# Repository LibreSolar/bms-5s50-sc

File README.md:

# BMS 5s (12 V)

Battery management system for up to 5 Li-ion cells based on bq76920 IC from Texas Instruments

## Boards

The Libre Solar BMS is divided into two different boards, connected via a flat cable and integrated into one housing.

### Control board (BMS 5s)

[Schematic (PDF)](power-pcb/Switch-N-Sense.pdf)

### Power board (Switch-N-Sense)

[Schematic (PDF)](control-pcb/BMS-5s.pdf)

## Features

- 3 to 5 Li-ion cells (e.g. LiFePO4)
- 50 A maximum current
- Balancing current approx. 150 mA
- STM32F072 ARM Cortex M0 microcontroller
- Built-in CAN communication interface and UEXT extension connector

## Housing

The BMS should fit into a Hammond Mfg 1591XXBFL housing as shown in below picture. The picture shows the BMS controller PCB with the Switch-N-Sense power PCB stacked on top of it:

## History

- There is [another version of the BMS](https://github.com/LibreSolar/BMS48V)  supporting more cells and developed in Eagle CAD. This one is the first of the new BMS generation developed in KiCad. An updated version of the versions with higher number of cells might come soon.

## Important Notice

The PCBs have not been tested regarding EMC and other regulations. If you reproduce the boards, you use them at your own risk and responsibility.

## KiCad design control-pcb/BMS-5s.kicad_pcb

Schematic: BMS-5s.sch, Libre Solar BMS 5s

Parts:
LOGO1: OPEN_HARDWARE; OSHW-Logo_5.7x6mm_SilkScreen
LOGO2: LIBRE_SOLAR; LIBRESOLAR_LOGO
P1: Conn_Switch-N-Sense; Wuerth_WR-FPC_686112148922; PartNumber 686112148922
P2: CONN_01X06; Phoenix_Contact_MC_1,5_6-G-3,81; PartNumber 1803316
TP3: Load+; TestPoint_0.8mm_hole
TP4: Bat+; TestPoint_0.8mm_hole
TP5: Regout; TestPoint_0.8mm_hole
TP6: SDA; TestPoint_0.8mm_hole
TP7: SCL; TestPoint_0.8mm_hole

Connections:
/Analog Frontend/BAT+: P1.1, TP4.1; also elsewhere on the board
/Analog Frontend/LOAD+: P1.2, TP3.1; also elsewhere on the board
/BQ76920/CELLS_0: P2.6; also elsewhere on the board
/BQ76920/CELLS_1: P2.5; also elsewhere on the board
/BQ76920/CELLS_2: P2.4; also elsewhere on the board
/BQ76920/CELLS_3: P2.3; also elsewhere on the board
/BQ76920/CELLS_4: P2.2; also elsewhere on the board
/BQ76920/CELLS_5: P2.1; also elsewhere on the board
/BQ76920/CHG_EN: P1.4; also elsewhere on the board
/BQ76920/DSG_EN: P1.5; also elsewhere on the board
/BQ76920/R_SENSE+: P1.7; also elsewhere on the board
/BQ76920/R_SENSE-: P1.8; also elsewhere on the board
/MCU/I2C2_SCL: TP7.1; also elsewhere on the board
/MCU/I2C2_SDA: TP6.1; also elsewhere on the board
/PCHG_EN: P1.6; also elsewhere on the board
/REGOUT: TP5.1; also elsewhere on the board
/TS1: P1.9; also elsewhere on the board
GND: P1.3, P1.10; also elsewhere on the board

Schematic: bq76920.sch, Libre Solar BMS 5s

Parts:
C1, C2, C3, C4, C5, C6, C11, C12, C13, C14: 100n; C_0603_1608; PartNumber CC0603KRX7R9BB104
C7, C9: 1u; C_0805_2012; PartNumber CC0805KKX7R9BB105
C8: 10u; C_0805_2012; PartNumber GRM21BR61E106KA73L
C10: 4.7u; C_0603_1608; PartNumber GRM188R61A475KE15D
D1, D2, D3, D4, D5, D7: 5.6V; D_SOD-323; PartNumber MM3Z5V6T1G
D6, D8: 1N4148WS-7-F; D_SOD-323; PartNumber 1N4148WS-7-F
D9, D10, D11, D12: 3.3V; D_SOD-323; PartNumber MM3Z3V3T1G
P3: ON/OFF; Phoenix_Contact_MC_1,5_2-G-3,81; PartNumber 1803277
Q1, Q3, Q5, Q6, Q7: DMN2004K; SOT-23; PartNumber DMN2004K-7
Q2: BSS84; SOT-23; PartNumber BSS84
Q4: BSS138; SOT-23; PartNumber BSS138
R1, R2, R3, R4, R5: 33; R_2010_5025; PartNumber RC2010JK-0733RL
R6, R7, R8, R9, R10, R11, R20, R25, R26: 1k; R_0603_1608; PartNumber RC0603FR-071KL
R12, R13, R14, R15, R16, R22: 10k; R_0603_1608; PartNumber RC0603FR-0710KL
R17: 100; R_0603_1608; PartNumber RC0603FR-07100RL
R18, R19, R24: 100k; R_0603_1608; PartNumber RC0603FR-07100KL
R21: 1M; R_0603_1608; PartNumber RC0603FR-071ML
R23: 5.6K; R_0603_1608; PartNumber RC0603FR-075K6L
R49, R50: 2.2k; R_0603_1608; PartNumber RC0603FR-072K2L
SW1: SW_PUSH; SW_Tactile_SKHH_Angled; PartNumber 431256083716
U1: BQ76920; TSSOP-20_4.4x6.5mm_P0.65mm; PartNumber BQ7692003PWR

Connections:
+3V3: R49.2, R50.2; also elsewhere on the board
/Analog Frontend/BAT+: D7.1, Q2.2, R18.2; also elsewhere on the board
/BQ76920/BTN_PWR: D10.1, R22.2, R24.1; also elsewhere on the board
/BQ76920/CELLS_0: D1.2, Q7.2 (S), R6.2; also elsewhere on the board
/BQ76920/CELLS_1: D2.2, P3.1, Q6.2 (S), R1.2, R7.2, SW1.1; also elsewhere on the board
/BQ76920/CELLS_2: D3.2, Q5.2 (S), R2.2, R8.2; also elsewhere on the board
/BQ76920/CELLS_3: D4.2, Q3.2 (S), R3.2, R9.2; also elsewhere on the board
/BQ76920/CELLS_4: D5.2, Q1.2 (S), R4.2, R10.2; also elsewhere on the board
/BQ76920/CELLS_5: D6.2 (A), R5.2, R11.2; also elsewhere on the board
/BQ76920/CHG_EN: U1.2 (CHG); also elsewhere on the board
/BQ76920/DSG_EN: U1.1 (DSG); also elsewhere on the board
/BQ76920/REGSRC: C9.1, D6.1 (K), Q2.3, R17.1, U1.9 (REGSRC)
/BQ76920/R_SENSE+: R25.2; also elsewhere on the board
/BQ76920/R_SENSE-: R26.1; also elsewhere on the board
/BQ76920/SRN: C12.2, C14.1, D12.1, R26.2, U1.19 (SRN)
/BQ76920/SRP: C12.1, C13.1, D11.1, R25.1, U1.18 (SRP)
/BQ76920/VC0: C1.2, D9.1, R6.1, R12.2, U1.17 (VC0)
/BQ76920/VC1: C2.1, C3.2, R7.1, R13.2, U1.16 (VC1)
/BQ76920/VC2: C3.1, C4.2, R8.1, R14.2, U1.15 (VC2)
/BQ76920/VC3: C4.1, C5.2, R9.1, R15.2, U1.14 (VC3)
/BQ76920/VC4: C5.1, C6.2, R10.1, R16.2, U1.13 (VC4)
/BQ76920/VC5: C6.1, R11.1, U1.12 (VC5)
/MCU/ALERT_IN: R20.1; also elsewhere on the board
/MCU/I2C2_SCL: R50.1, U1.5 (SCL); also elsewhere on the board
/MCU/I2C2_SDA: R49.1, U1.4 (SDA); also elsewhere on the board
/REGOUT: C10.1, Q4.1 (G), U1.8 (REGOUT); also elsewhere on the board
/TS1: C11.1, R23.2, U1.6 (TS1); also elsewhere on the board
GND: C1.1, C2.2, C7.2, C8.2, C9.2, C10.2, C11.2, C13.2, C14.2, D9.2, D10.2, D11.2, D12.2, Q4.2 (S), R21.2, R24.2, U1.3 (VSS); also elsewhere on the board
unnamed: C7.1, U1.7 (CAP1)
unnamed: C8.1, R17.2, U1.10 (BAT)
unnamed: D1.1, Q7.1 (G), R12.1
unnamed: D2.1, Q6.1 (G), R13.1
unnamed: D3.1, Q5.1 (G), R14.1
unnamed: D4.1, Q3.1 (G), R15.1
unnamed: D5.1, Q1.1 (G), R16.1
unnamed: D7.2, Q2.1, R18.1, R19.2
unnamed: D8.1 (K), R23.1
unnamed: D8.2 (A), P3.2, R22.1, SW1.2
unnamed: Q1.3 (D), R5.1
unnamed: Q3.3 (D), R4.1
unnamed: Q4.3 (D), R19.1
unnamed: Q5.3 (D), R3.1
unnamed: Q6.3 (D), R2.1
unnamed: Q7.3 (D), R1.1
unnamed: R20.2, R21.1, U1.20 (ALERT)

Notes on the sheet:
Temperature sensor
Balancing (33R resistors) Current: 100-130 mA (3.3-4.2 V) Heat dissipation: 300-600 mW
ALERT pin from BQ769x0 drives interupt in case of new current reading or battery error
Current sense filter
Supply BQ via cell 5 only if BAT+ connector not yet present and system shut down
2-5V
> 1V needed for boot-up
Boot Switch
Balancing circuits
I2C pull-ups

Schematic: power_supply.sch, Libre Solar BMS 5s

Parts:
C15, C18: 100n; C_0603_1608; PartNumber CC0603KRX7R9BB104
C16, C21: 1u; C_0805_2012; PartNumber CC0805KKX7R9BB105
C17: 4.7u; C_1206_3216; PartNumber GRM31CR71H475MA12L
C19, C20: 10u; C_0805_2012; PartNumber GRM21BR61E106KA73L
C22: 4.7u; C_0603_1608; PartNumber GRM188R61A475KE15D
C23: 100p; C_0603_1608; PartNumber CC0603JRNPO9BN101
D13: 1N4148WS-7-F; D_SOD-323; PartNumber 1N4148WS-7-F
D14: SS16FP; D_PowerDI-123; PartNumber SS16FP
L1: 4.7uH; L_0805_2012Metric; PartNumber LQM21PN4R7NGRD
L2: 22uH; L_WE-TPC-4818; PartNumber SRR4028-220Y
R27: 52.3k; R_0603_1608; PartNumber RC0603FR-0752K3L
R28: 10k; R_0603_1608; PartNumber RC0603FR-0710KL
TP1: 5V; TestPoint_0.8mm_hole
TP2: 3.3V; TestPoint_0.8mm_hole
U2: MCP16331-CH; SOT-23-6; PartNumber MCP16331T-E/CH
U3: AP2210-3.3; SOT-23-5; PartNumber AP2210K-3.3TRG1

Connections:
+3V3: C22.1, TP2.1, U3.5; also elsewhere on the board
+5V: C19.1, C20.1, C21.1, D13.2 (A), L2.2, R27.1, TP1.1, U3.1, U3.3; also elsewhere on the board
/Analog Frontend/BAT+: C16.1, L1.1; also elsewhere on the board
/REGOUT: U2.4; also elsewhere on the board
GND: C16.2, C17.2, C18.2, C19.2, C20.2, C21.2, C22.2, C23.2, D14.2 (A), R28.2, U2.2, U3.2; also elsewhere on the board
unnamed: C15.1, D13.1 (K), U2.1
unnamed: C15.2, D14.1 (K), L2.1, U2.6
unnamed: C17.1, C18.1, L1.2, U2.5
unnamed: C23.1, U3.4
unnamed: R27.2, R28.1, U2.3

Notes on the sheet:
Max current output: 150mA
25V
Battery to 5V (SMPS)
5V to 3.3V (LDO)

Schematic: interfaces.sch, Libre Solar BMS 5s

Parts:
C24, C25, C26: 100n; C_0603_1608; PartNumber CC0603KRX7R9BB104
D15: USBLC6-2SC6; SOT-23-6; PartNumber USBLC6-2SC6
D16: NUP2105L; SOT-23; PartNumber NUP2105LT1G
J2: UEXT; Box_Header_2x05x2.54mm_Straight; PartNumber 61201021621
JP1: Jumper_NC_Small; PinHeader_2x01_P2.54mm_Horizontal
JP2, JP3: RJ45_NS; RJ45_8P8C; PartNumber 54602-908LF
P4: USB_Micro-B; USB_Micro-B_10103594-0001LF; PartNumber 10103594-0001LF
R31: 100k; R_0603_1608; PartNumber RC0603FR-07100KL
R32: 120; R_1206_3216; PartNumber RC1206FR-07120RL
R33, R34: 2.2k; R_0603_1608; PartNumber RC0603FR-072K2L
RT1: 200mA; R_1206_3216; PartNumber 0ZCJ0020FF2E
U4: TJA1042T/3; SOIC-8_3.9x4.9mm_Pitch1.27mm; PartNumber TJA1042T/3/1J

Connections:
+3V3: C25.1, J2.1 (3V3), R33.2, R34.2, U4.5; also elsewhere on the board
+5V: C24.1, RT1.1, U4.3; also elsewhere on the board
/Communication/CAN_GND: JP2.3, JP2.7, JP3.3, JP3.7
/Communication/CAN_H: D16.1, JP1.2, JP2.1, JP3.1, U4.7
/Communication/CAN_L: D16.2, JP2.2, JP3.2, R32.2, U4.6
/Communication/CAN_RX: U4.4; also elsewhere on the board
/Communication/CAN_SHLD: JP2.6, JP3.6
/Communication/CAN_STB: U4.8; also elsewhere on the board
/Communication/CAN_TX: U4.1; also elsewhere on the board
/Communication/CAN_V+: JP2.8, JP3.8
/Communication/RJ45_P4: JP2.4, JP3.4
/Communication/RJ45_P5: JP2.5, JP3.5
/Communication/UEXT_RX: J2.4 (RXD); also elsewhere on the board
/Communication/UEXT_TX: J2.3 (TXD); also elsewhere on the board
/Communication/USB_DM: D15.3 (IO2); also elsewhere on the board
/Communication/USB_DP: D15.1 (IO1); also elsewhere on the board
/MCU/I2C1_SCL: J2.5 (SCL), R34.1; also elsewhere on the board
/MCU/I2C1_SDA: J2.6 (SDA), R33.1; also elsewhere on the board
/MCU/SPI1_MISO: J2.7 (MISO); also elsewhere on the board
/MCU/SPI1_MOSI: J2.8 (MOSI); also elsewhere on the board
/MCU/SPI1_SCK: J2.9 (SCK); also elsewhere on the board
/MCU/SSEL: J2.10 (SSEL); also elsewhere on the board
GND: C24.2, C25.2, C26.1, D15.2 (GND), D16.3, J2.2 (GND), P4.5 (GND), R31.2, U4.2; also elsewhere on the board
unnamed: C26.2, P4.6 (shield)
unnamed: D15.4 (IO2), P4.2 (D-)
unnamed: D15.5 (VBUS), P4.1 (VCC), RT1.2
unnamed: D15.6 (IO1), P4.3 (D+)
unnamed: JP1.1, R32.1
unnamed: P4.4 (ID), R31.1

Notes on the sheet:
CAN interface
Extension connector
I2C pull-ups
USB connector
DNP

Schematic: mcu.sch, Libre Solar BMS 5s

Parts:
C27, C31, C32, C33, C34, C36: 100n; C_0603_1608; PartNumber CC0603KRX7R9BB104
C30, C35: 4.7u; C_0603_1608; PartNumber GRM188R61A475KE15D
D17: LM4040CYM3-2.5; SOT-23; PartNumber LM4040DYM3-2.5-TR
L3: L; R_0603_1608; PartNumber BLM18AG601SN1D
LED1, LED2: LED; LED_D3.0mm
LED3, LED4: LED; LED_0603_1608Metric
P5: CONN_01X02; PinHeader_1x02_P2.54mm_Vertical
Q8: BSS138; SOT-23; PartNumber BSS138
R35, R37: 1M; R_0603_1608; PartNumber RC0603FR-071ML
R38: 2.2k; R_0603_1608; PartNumber RC0603FR-072K2L
R39: 52.3k; R_0603_1608; PartNumber RC0603FR-0752K3L
R40: 10k; R_0603_1608; PartNumber RC0603FR-0710KL
R41, R42: 330; R_0603_1608; PartNumber RC0603FR-07330RL
SW2: SW_PUSH; SW_SPST_EVQP7A; PartNumber 434121050816
SWD1: ST_Nucleo_SWD; PinHeader_1x06_P2.54mm_Vertical
U5: STM32F072CB; LQFP-48_7x7mm_P0.5mm; PartNumber STM32F072CBT6
U6: 24AA01; SOT-23-5; PartNumber 24AA01T-I/OT
Y1: 8kHz; Resonator_Murata_CSTCE_G; Tolerance 0.1%; PartNumber CSTCE8M00G15C99-R0

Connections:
+3V3: C32.1, C33.1, C34.1, C35.1, C36.1, L3.1, R35.2, R37.2, R40.2, SWD1.1, U5.1 (VBAT), U5.24 (VDD_1), U5.36 (VDD_2), U5.48 (VDD_3), U6.4; also elsewhere on the board
/Analog Frontend/TEMP_1: U5.16 (PA6); also elsewhere on the board
/Analog Frontend/TEMP_2: U5.17 (PA7); also elsewhere on the board
/Analog Frontend/V_BAT: U5.14 (PA4); also elsewhere on the board
/Analog Frontend/V_LOAD: U5.15 (PA5); also elsewhere on the board
/BQ76920/BTN_PWR: U5.29 (PA8); also elsewhere on the board
/Communication/CAN_RX: U5.45 (PB8); also elsewhere on the board
/Communication/CAN_STB: U5.38 (PA15); also elsewhere on the board
/Communication/CAN_TX: U5.46 (PB9); also elsewhere on the board
/Communication/UEXT_RX: U5.13 (PA3); also elsewhere on the board
/Communication/UEXT_TX: U5.12 (PA2); also elsewhere on the board
/Communication/USB_DM: U5.32 (PA11); also elsewhere on the board
/Communication/USB_DP: U5.33 (PA12); also elsewhere on the board
/MCU/ALERT_IN: U5.25 (PB12); also elsewhere on the board
/MCU/BOOT0: C30.1, R35.1, R38.2, U5.44 (BOOT0)
/MCU/I2C1_SCL: U5.42 (PB6); also elsewhere on the board
/MCU/I2C1_SDA: U5.43 (PB7); also elsewhere on the board
/MCU/I2C2_SCL: U5.21 (PB10), U6.1; also elsewhere on the board
/MCU/I2C2_SDA: U5.22 (PB11), U6.3; also elsewhere on the board
/MCU/LED1: R41.2, U5.27 (PB14)
/MCU/LED2: R42.2, U5.28 (PB15)
/MCU/OSC_IN: U5.5 (PD0-OSC_IN), Y1.1
/MCU/OSC_OUT: U5.6 (PD1-OSC_OUT), Y1.3
/MCU/SPI1_MISO: U5.40 (PB4); also elsewhere on the board
/MCU/SPI1_MOSI: U5.41 (PB5); also elsewhere on the board
/MCU/SPI1_SCK: U5.39 (PB3); also elsewhere on the board
/MCU/SSEL: U5.11 (PA1); also elsewhere on the board
/MCU/SWCLK: SWD1.2, U5.37 (PA14)
/MCU/SWDIO: SWD1.4, U5.34 (PA13)
/MCU/USART1_RX: P5.2, U5.31 (PA10)
/MCU/USART1_TX: P5.1, U5.30 (PA9)
/MCU/V_REF: D17.1, R40.1, U5.10 (PA0-WKUP)
/MCU/~RESET: C31.1, R37.1, R39.1, SW2.1, SWD1.5, U5.7 (NRST)
/PCHG_EN: U5.20 (PB2); also elsewhere on the board
/TS1: U5.26 (PB13); also elsewhere on the board
GND: C27.2, C30.2, C31.2, C32.2, C33.2, C34.2, C35.2, C36.2, D17.2, LED1.1, LED2.1, LED3.1, LED4.1, Q8.2 (S), SW2.2, SWD1.3, U5.8 (VSSA), U5.23 (VSS_1), U5.35 (VSS_2), U5.47 (VSS_3), U6.2, U6.5, Y1.2; also elsewhere on the board
unnamed: C27.1, L3.2, U5.9 (VDDA)
unnamed: LED1.2, LED3.2, R41.1
unnamed: LED2.2, LED4.2, R42.1
unnamed: Q8.1 (G), R39.2
unnamed: Q8.3 (D), R38.1

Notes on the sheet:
Status LEDs
MCU STM32F072
STM Nucleo SWD and USART
Equations: tau = R39 * C36 = 2.2 s V(t) = Vmax * (1-exp(-t/tau)) --> t = -tau * ln(1-V/Vmax) Normal startup: BOOT0 < 0.69 V Press SW1 < 0.51 s USB bootloader: BOOT0 > 1.61 V Press SW1 > 1.47 s
min. 65 uA operating current
Voltage reference
MCU reset and boot circuit
Tight tolerance for CAN interface
BQ769x0 ID either 0x08 or 0x18 24AA01 has 0b1010XXX --> OK
EEPROM

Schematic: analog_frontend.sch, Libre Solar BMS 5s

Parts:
C37, C38, C39, C40: 100n; C_0603_1608; PartNumber CC0603KRX7R9BB104
D18, D19, D20, D21: 3.3V; D_SOD-323; PartNumber MM3Z3V3T1G
P6, P7: CONN_01X02; Phoenix_Contact_MC_1,5_2-G-3,81; PartNumber 1803277
R43, R44: 100k; R_0603_1608; PartNumber RC0603FR-07100KL
R45, R46, R47, R48: 10k; R_0603_1608; PartNumber RC0603FR-0710KL

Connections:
+3V3: R47.1, R48.1; also elsewhere on the board
/Analog Frontend/BAT+: R43.1; also elsewhere on the board
/Analog Frontend/LOAD+: R44.1; also elsewhere on the board
/Analog Frontend/TEMP_1: C39.1, D18.1, P6.1, R47.2; also elsewhere on the board
/Analog Frontend/TEMP_2: C40.1, D19.1, P7.1, R48.2; also elsewhere on the board
/Analog Frontend/V_BAT: C37.1, D20.1, R43.2, R45.1; also elsewhere on the board
/Analog Frontend/V_LOAD: C38.1, D21.1, R44.2, R46.1; also elsewhere on the board
GND: C37.2, C38.2, C39.2, C40.2, D18.2, D19.2, D20.2, D21.2, P6.2, P7.2, R45.2, R46.2; also elsewhere on the board

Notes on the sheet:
If not stated otherwise, all MLCC 50V X7R
Temperature (ext./int.)
Battery and load voltage
Maximum voltage: 5*4.2V = 21V

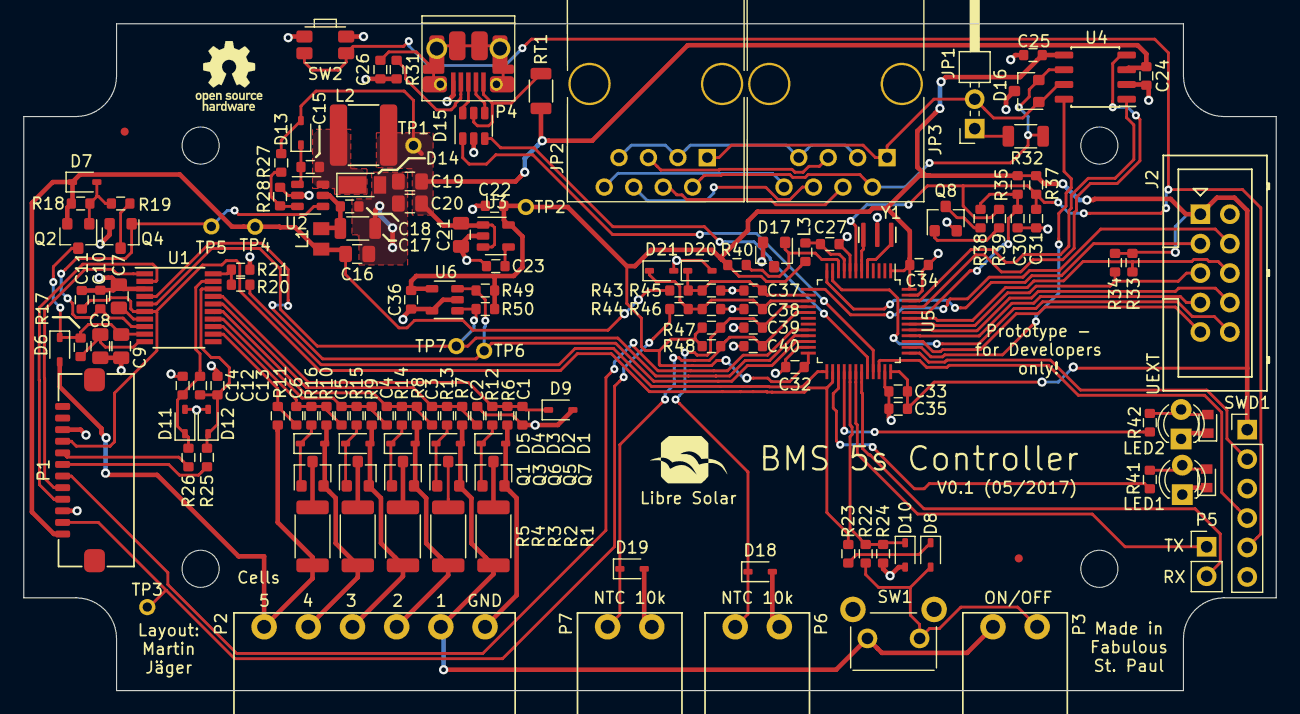
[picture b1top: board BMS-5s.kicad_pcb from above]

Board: 2 copper layers, 108.0 x 57.5 mm, 152 parts (0 on the bottom side), 99 nets.

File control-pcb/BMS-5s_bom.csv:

Component,Description,Part,References,Value,Footprint,Quantity Per PCB,Datasheet,PartNumber,Manufacturer,Remarks,Alternative,Tolerance
1,Unpolarized capacitor,C,C1 C2 C3 C4 C5 C6 C11 C12 C13 C14 C15 C18 C24 C25 C26 C27 C31 C32 C33 C34 C36 C37 C38 C39 C40,100n,C_0603_1608,25,,GRM188R71H104KA93D,Murata,,,
2,Unpolarized capacitor,C,C23,100p,C_0603_1608,1,,GRM1885C2A101JA01D,Murata,,,
3,Unpolarized capacitor,C,C8 C19 C20,10u,C_0805_2012,3,,GRM21BR61E106KA73L,Murata,,,
4,Unpolarized capacitor,C,C7 C9 C16 C21,1u,C_0603_1608,4,,GRM188R61H105KAALD,Murata,X5R,,
5,Unpolarized capacitor,C,C10 C22 C30 C35,4.7u,C_0603_1608,4,,GRM188R61A475KE15D,Murata,10V,,
6,Unpolarized capacitor,C,C17,4.7u,C_1206_3216,1,,GRM31CR71H475MA12L,Murata,,,
7,Diode,D,D6 D8 D13,1N4148W-7-F,D_SOD-323,3,,1N4148W-7-F,Diodes Inc.,,,
8,Diode zener,D_Zener,D9 D10 D11 D12 D18 D19 D20 D21,3.3V,D_SOD-323,8,,MM3Z3V3T1G,ON Semiconductor,,,
9,Diode zener,D_Zener,D1 D2 D3 D4 D5 D7,5.6V,D_SOD-323,6,,MM3Z5V6T1G,ON Semiconductor,,BZX384-C5V6,
10,,LM4040,D17,LM4040CYM3-2.5,SOT-23,1,,LM4040DYM3-2.5-TR,Microchip,,,
11,,NUP2105L,D16,NUP2105L,SOT-23,1,,NUP2105LT1G,ON Semiconductor,,,
12,Diode Schottky,D_Schottky,D14,SS16FP,D_PowerDI-123,1,,SS16FP,Diodes Inc.,,DFLS160-7,
13,,USBLC6-2SC6,D15,USBLC6-2SC6,SOT-23-6,1,,USBLC6-2SC6,STMicroelectronics,,WE-TVS 82400102,
14,,UEXT,J2,UEXT,Box_Header_2x05x2.54mm_Straight,1,,61201021621,Würth,,,
15,Jumper normally close,Jumper_NC_Small,JP1,Jumper_NC_Small,Pin_Header_Angled_2x01_Pitch2.54mm,1,,,,,,
16,,RJ45_NS,JP2 JP3,RJ45_NS,RJ45_8P8C,2,,54602-908LF,Amphenol FCI,,,
17,Inductor,L,L2,22uH,L_WE-TPC-4818,1,,SRR4028-220Y,Bourns,,WE-TPC-4818 744042220,
18,Inductor,L,L1,4.7uH,L_0805,1,,LQM21PN4R7NGRD,Murata,,,
19,Inductor,L,L3,L,R_0603_1608,1,,BLM18AG601SN1D,Murata,,,
20,,LED,LED1 LED2,LED,LED_D3.0mm,2,,,,,,
21,Libre Solar Logo,LIBRE_SOLAR,LOGO2,LIBRE_SOLAR,LIBRESOLAR_LOGO,1,,,,,,
22,Open Hardware Logo,OPEN_HARDWARE_1,LOGO1,OPEN_HARDWARE_1,OSHW-Logo_5.7x6mm_SilkScreen,1,,,,,,
23,"Connector, single row, 01x02, pin header",CONN_01X02,P5,CONN_01X02,Pin_Header_Straight_1x02_Pitch2.54mm,1,,,,,,
24,"Connector, single row, 01x02, pin header",CONN_01X02,P6 P7,CONN_01X02,"Phoenix_Contact_PTSM_0.5_2-HH-2,5-THR-R16",2,,,,,,
25,"Connector, single row, 01x06, pin header",CONN_01X06,P2,CONN_01X06,"Phoenix_Contact_MC_1,5_6-G-3,81",1,,1803316,Phoenix Contact,"MC 1,5/ 6-G-3,81",,
26,,Conn_Switch-N-Sense,P1,Conn_Switch-N-Sense,Wuerth_WR-FPC_687112149022,1,,687112149022,Würth,,,
27,"Connector, single row, 01x02, pin header",CONN_01X02,P3,ON/OFF,"Phoenix_Contact_PTSM_0.5_2-HH-2,5-THR-R16",1,,,Phoenix Contact,,,
28,,USB_OTG,P4,USB_Micro-B,USB_Micro-B_10103594-0001LF,1,,10103594-0001LF,FCI,,,
29,Transistor N-MOSFETwith substrate diode (general),Q_NMOS_GSD,Q4 Q8 Q9,2N7002,SOT-23,3,,"2N7002,215",Nexperia,,,
30,Transistor N-MOSFETwith substrate diode (general),Q_NMOS_GSD,Q2,BSS84,SOT-23,1,,BSS84,Fairchild Semiconductor,,,
31,Transistor N-MOSFETwith substrate diode (general),Q_NMOS_GSD,Q1 Q3 Q5 Q6 Q7,DMN2004K,SOT-23,5,,DMN2004K-7,Diodes Incorporated,,,
32,Resistor,R,R17,100,R_0603_1608,1,,RC0603FR-07100RL,Yageo,,,
33,Resistor,R,R18 R19 R24 R31 R43 R44,100k,R_0603_1608,6,,RC0603FR-07100KL,Yageo,,,
34,Resistor,R,R12 R13 R14 R15 R16 R22 R28 R40 R45 R46 R47 R48,10k,R_0603_1608,12,,RC0603FR-0710KL,Yageo,,,
35,Resistor,R,R32,120,R_1206_3216,1,,RC1206FR-07120RL,Yageo,,,
36,Resistor,R,R21 R35 R37,1M,R_0603_1608,3,,RC0603FR-071ML,Yageo,,,
37,Resistor,R,R6 R7 R8 R9 R10 R11 R20 R25 R26,1k,R_0603_1608,9,,RC0603FR-071KL,Yageo,,,
38,Resistor,R,R33 R34 R38 R49 R50,2.2k,R_0603_1608,5,,RC0603FR-072K2L,Yageo,,,
39,Resistor,R,R1 R2 R3 R4 R5,33,R_2010_5025,5,,RC2010JK-0733RL,Yageo,,,
40,Resistor,R,R41 R42,330,R_0603_1608,2,,RC0603FR-07330RL,Yageo,,,
41,Resistor,R,R23,5.6K,R_0603_1608,1,,RC0603FR-075K6L,Yageo,,,
42,Resistor,R,R27 R39,52.3k,R_0603_1608,2,,RC0603FR-0752K3L,Yageo,,,
43,,R_PTC,RT1,200mA,R_0805_2012,1,,0805L020,Littelfuse,,,
44,Button,SW_PUSH,SW1,SW_PUSH,SW_Tactile_SKHH_Angled,1,,431256083716,Würth,,,
45,Button,SW_PUSH,SW2,SW_PUSH,SW_SPST_EVQP7A,1,,434121050816,Würth,,,
46,,ST_Nucleo_SWD,SWD1,ST_Nucleo_SWD,Pin_Header_Straight_1x05_Pitch2.54mm,1,,,,,,
47,Microchip 24AA01 1K I2C EEPROM,24AA01,U6,24AA01,SOT-23-5,1,,24AA01,Microchip,,,
48,"300mA low dropout linear regulator, shutdown pin, 1.5V fixed positive output, SOT-23-5 package",AP2210-3.3,U3,AP2210-3.3,SOT-23-5,1,http://www.diodes.com/_files/datasheets/AP131.pdf,AP2210K-3.3TRG1,Diodes Inc.,,MIC5225,
49,,BQ76920,U1,BQ76920,TSSOP-20_4.4x6.5mm_Pitch0.65mm,1,,BQ7692003PWR,Texas Instruments,,,
50,"High-Voltage Input Integrated Switch Step-Down Regulator, 50V, 500mA",MCP16331-CH,U2,MCP16331-CH,SOT-23-6,1,http://ww1.microchip.com/downloads/en/DeviceDoc/20005308C.pdf,MCP16331T-E/CH,Microchip,,,
51,,STM32F072CB,U5,STM32F072CB,LQFP-48_7x7mm_Pitch0.5mm,1,,STM32F072CBT6,STMicroelectronics,,,
52,"TJA1042T/3, High-Speed CAN Transceiver, separate VIO, standby mode, SOIC-8",TJA1042T/3,U4,TJA1042T/3,SOIC-8_3.9x4.9mm_Pitch1.27mm,1,http://www.nxp.com/documents/data_sheet/TJA1042.pdf,TJA1042T/3/1J,NXP,,,
53,Two pin crystal,Resonator,Y1,8kHz,Resonator_Murata_CSTCE,1,,CSTCE8M00G15C99-R0,Murata,,,0.1%





Component Groups:,53
Component Count:,144
Fitted Components:,144
Number of PCBs:,1
Total components:,144
Schematic Version:,0.1b
Schematic Date:,3 dec 2016
BoM Date:,22/05/2017 16:05:45
Schematic Source:,D:\LibreSolar\2_Development\04_Hardware\BMS-5s\BMS-5s.sch
KiCad Version:,Eeschema (2017-05-10 revision 747583606)-makepkg

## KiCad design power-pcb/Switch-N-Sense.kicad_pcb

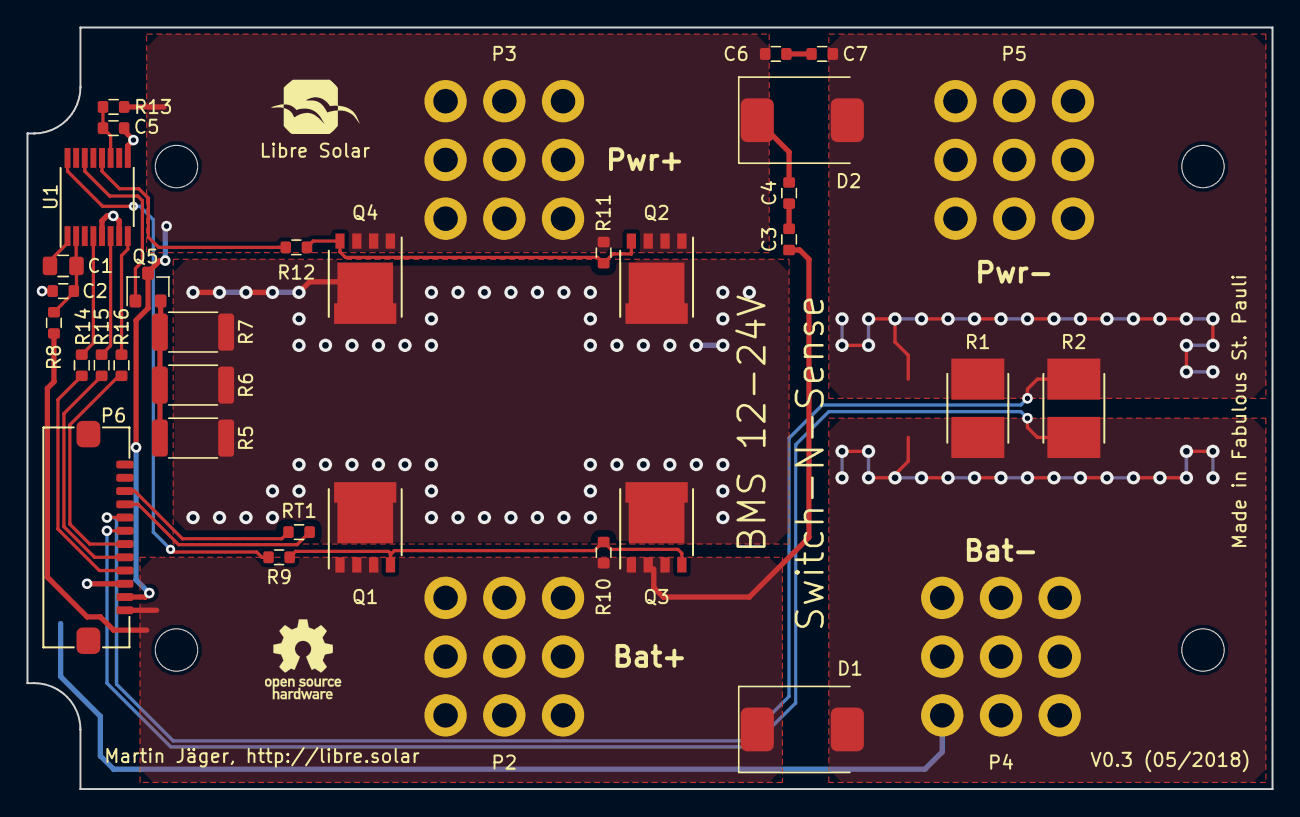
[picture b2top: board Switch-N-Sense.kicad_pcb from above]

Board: 2 copper layers, 94.0 x 57.5 mm, 37 parts (0 on the bottom side), 24 nets.

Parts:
C1: 1u; C_0805_2012
C2, C5: 10n; C_0603_1608
C3, C4, C6, C7: 100n; C_0603_1608
D1, D2: SMCJ24A; D_SMC
LOGO1: LIBRE_SOLAR; LIBRESOLAR_LOGO
LOGO2: OPEN_HARDWARE_1; OSHW-Logo_5.7x6mm_SilkScreen
P2, P3, P4, P5: CONN_01X01; Wuerth_WP-THRBU
P6: Conn_Switch-N-Sense; Wuerth_WR-FPC_686112148922
Q1, Q2, Q3, Q4: BSC014N04LS; 5X6_MOSFET
Q5: ZXMP6A13F; SOT-23
R1, R2: 2m; R_Bourns_CRE2512
R5, R6, R7: 330; R_2010_5025
R8, R13: 100; R_0603_1608
R9, R12: 4.7; R_0603_1608
R10, R11: 1M; R_0603_1608
R14, R15, R16: 1k; R_0603_1608
RT1: 10k; R_0603_1608
U1: BQ76200; TSSOP-16_4.4x5mm_P0.65mm

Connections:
/BAT+: C3.1, D1.1, P2.1, P6.12, Q1.S, Q3.S, R8.2, R10.2
/CHG+: Q1.D, Q2.D, Q3.D, Q4.D, R5.2, R6.2, R7.2
/CHG_EN: R14.2, U1.4
/CHG_G: Q1.G, Q3.G, R9.1, R10.1
/DSG_EN: R15.2, U1.6
/DSG_G: Q2.G, Q4.G, R11.2, R12.1
/LOAD+: C4.2, C6.1, D2.1, P3.1, P6.11, Q2.S, Q4.S, Q5.3, R11.1, R13.2
/LOAD-: C7.2, D2.2, P5.1, P6.5, R1.1, R2.1
/PCHG_EN: R16.2, U1.8
/PCHG_G: Q5.1, U1.14
GND: C2.2, C5.2, D1.2, P4.1, P6.6, P6.10, R1.2, R2.2, U1.5, U1.7, U1.9
unnamed: C1.1, C2.1, R8.1, U1.2
unnamed: C1.2, U1.1
unnamed: C3.2, C4.1
unnamed: C5.1, R13.1, U1.11
unnamed: C6.2, C7.1
unnamed: P6.3, RT1.2
unnamed: P6.4, RT1.1
unnamed: P6.7, R16.1
unnamed: P6.8, R15.1
unnamed: P6.9, R14.1
unnamed: Q5.2, R5.1, R6.1, R7.1
unnamed: R9.2, U1.16
unnamed: R12.2, U1.12

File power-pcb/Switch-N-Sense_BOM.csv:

Component;Description;Part;References;Value;Footprint;Quantity Per PCB;Datasheet;PartNumber;Manufacturer;Remarks
1;Unpolarized capacitor;C;C3 C4 C6 C7;100n;C_0603_1608;4;;CC0603KRX7R9BB104;Yageo;
2;Unpolarized capacitor;C;C2 C5;10n;C_0603_1608;2;;CC0603KRX7R9BB103;Yageo;
3;Unpolarized capacitor;C;C1;1u;C_0805_2012;1;;CC0603KRX7R8BB105;Yageo;
4;Diode Schottky;D_Schottky;D1 D2;SMCJ24A;D_SMC;2;;SMCJ24A;Bourns;
5;;LibreSolar_Logo;LOGO1;LIBRE_SOLAR;LIBRESOLAR_LOGO;1;;;;
6;small Open Hardware Logo;Logo_Open_Hardware_Small;LOGO2;OPEN_HARDWARE_1;OSHW-Logo_5.7x6mm_SilkScreen;1;;;;
7;Generic connector, single row, 01x01, script generated (kicad-library-utils/schlib/autogen/connector/);Conn_01x01;P2 P3 P4 P5;CONN_01X01;Wuerth_WP-THRBU;4;;74650195;Wuerth;
8;;Conn_Switch-N-Sense_Inverted;P6;Conn_Switch-N-Sense;Wuerth_WR-FPC_686112148922;1;;686112148922;Wuerth;
9;Transistor N-MOSFET (general);Q_NMOS;Q1 Q2 Q3 Q4;BSC014N04LS;5X6_MOSFET;4;;BSC014N04LS;Infineon;
10;Transistor P-MOSFET with substrate diode (general);Q_PMOS_GSD;Q5;ZXMP6A13F;SOT-23;1;;ZXMP6A13FTA;Diodes Incorporated;-60V
11;Resistor;R;R8 R13;100;R_0603_1608;2;;RC0603FR-07100RL;Yageo;
12;Resistor;R;R10 R11;1M;R_0603_1608;2;;RC0603FR-071ML;Yageo;
13;Resistor;R;R14 R15 R16;1k;R_0603_1608;3;;RC0603FR-071KL;Yageo;
14;Resistor;R;R1 R2;2m;R_Bourns_CRE2512;2;;CRE2512-FZ-R002E-3;Bourns;
15;Resistor;R;R5 R6 R7;330;R_2010_5025;3;;RC2010JK-07330RL;Yageo;
16;Resistor;R;R9 R12;4.7;R_0603_1608;2;;RC0603FR-074R7L;Yageo;
17;;R_NTC;RT1;10k;R_0603_1608;1;;NTCG163JF103FT1S;TDK;
18;;BQ76200;U1;BQ76200;TSSOP-16_4.4x5mm_P0.65mm;1;;BQ76200PWR;Texas Instruments;





Component Groups:;18
Component Count:;37
Fitted Components:;37
Number of PCBs:;1
Total components:;37
Schematic Version:;0.2
Schematic Date:;
BoM Date:;11/05/2018 13:48:19
Schematic Source:;D:\LibreSolar\2_Development\04_Hardware\BMS-5s\power-pcb\Switch-N-Sense.sch
KiCad Version:;Eeschema (5.0.0-rc2-dev-444-g2974a2c10)

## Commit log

2017-06-01 Small fixes for final gerber export (DRU check passed)
2017-06-01 Switch-N-Sense (power PCB) added
2017-06-14 Issues #1, #2 and #4 fixed
2017-10-22 Issue #6 fixed
2017-10-22 Small changes in power PCB
2018-05-11 Update to KiCAD 5 and minor changes in part selection
2018-05-11 Gerber removed and BOM files added.
2018-05-11 Direct link to schematic added.
2018-07-03 Step file of control PCB added.
2018-10-15 DRC errors corrected
2018-10-20 Diode part number corrected, closing issue #9

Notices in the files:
BMS-5s.sch:
License: CC-BY-SA
